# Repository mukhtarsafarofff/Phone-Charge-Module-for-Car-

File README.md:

(ENG)   Actually the MC34063 is the heart of many products that today need a DC-DC converter, that is, a direct voltage converter. The MC34063 is an extremely versatile electronic component that has gained wide acceptance in the electronics world.

The circuit shows the MC34063 configuration as a step-down regulator and in this configuration the output voltage is given by the following formula :
Vout = 1.25 * (1 + R2 / R1)
In our case R2 = 3.6k and R1 = 1.2K so Vout gives us exactly 5 Volts! To transform our circuit into a USB charger, simply connect a USB terminal to the output by soldering the cables with the correct pinout.  Its versatility is accompanied by a very convenient price which is an interesting combination. It is a switching regulator that, unlike linear regulators (such as the LM7805), does not dissipate much heat. In my case, my phone needs a charger at 5VDC, that is, the same voltage that a USB port provides us. Because of this, my faulty charger circuit was designed to provide such a voltage at a current of 500mA. That is, it is an oscillator that chops (or divides into portions) the input voltage, according to the required output voltage value want.

(DEU)  Tatsächlich ist der MC34063 das Herzstück vieler Produkte, die heute einen DC-DC-Wandler benötigen, also einen Gleichspannungswandler. Der MC34063 ist eine äußerst vielseitige elektronische Komponente, die in der Elektronikwelt weit verbreitet und akzeptiert ist. Seine Vielseitigkeit ist mit einem sehr günstigen Preis verbunden, was eine interessante Kombination darstellt.  Es handelt sich um einen Schaltregler, der im Gegensatz zu linearen Reglern (wie dem LM7805) nicht viel Wärme abgibt. In meinem Fall benötigt mein Telefon ein Ladegerät mit 5 VDC, also der gleichen Spannung, die ein USB-Port liefert. Deshalb wurde mein fehlerhafter Ladegerätkreis so entworfen, dass er eine solche Spannung bei einem Strom von 500 mA liefert.  Mit einigen Änderungen können wir den Schaltkreis, den ich später besprechen werde, anpassen, um verschiedene Spannungen zu liefern. With a few changes we can adapt the circuit I will discuss later to provide different voltages.
The chip used is basically the heart of a switched power supply (or switching regulator).

Der verwendete Chip ist im Grunde das Herzstück eines Schaltnetzteils (oder Schaltreglers).Das heißt, er ist ein Oszillator, der die Eingangsspannung entsprechend dem benötigten Ausgangsspannungswert zerkleinert (oder in Portionen teilt).Die Schaltung zeigt die Konfiguration des MC34063 als Abwärtswandler, und in dieser Konfiguration wird die Ausgangsspannung durch die folgende Formel bestimmt:
Vout = 1,25 * (1 + R2 / R1)
In unserem Fall beträgt R2 = 3,6 k und R1 = 1,2 k, sodass Vout uns genau 5 Volt liefert! Um unseren Schaltkreis in ein USB-Ladegerät zu verwandeln,

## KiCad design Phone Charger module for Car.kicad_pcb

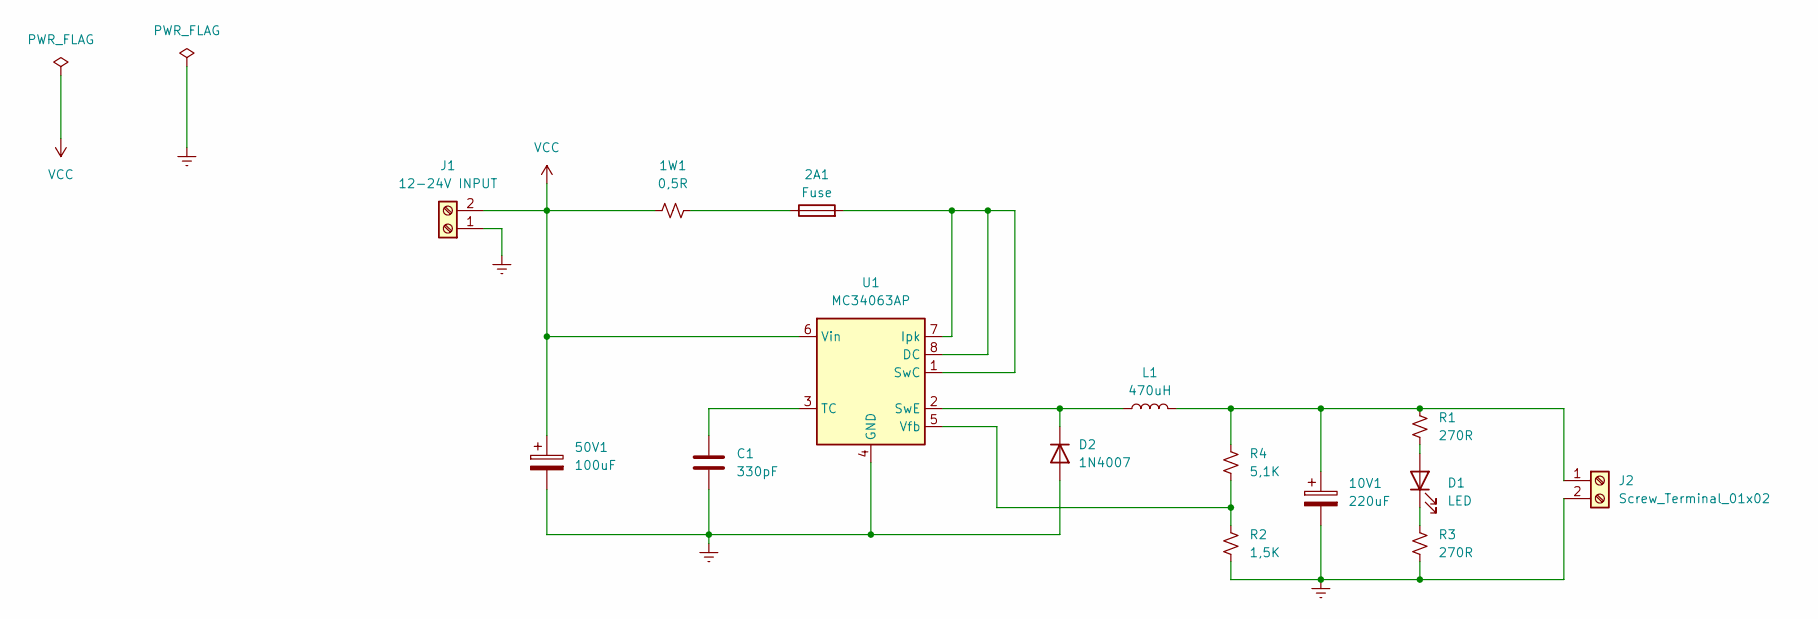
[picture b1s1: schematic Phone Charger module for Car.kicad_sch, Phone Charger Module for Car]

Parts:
1W1: 0,5R; R_Axial_DIN0614_L14.3mm_D5.7mm_P15.24mm_Horizontal
2A1: Fuse; Fuse_Bourns_MF-RG1000
10V1: 220uF; CP_Radial_D13.0mm_P7.50mm
50V1: 100uF; CP_Radial_D13.0mm_P7.50mm
C1: 330pF; C_Disc_D9.0mm_W5.0mm_P7.50mm
D1: LED; LED_D5.0mm
D2: 1N4007; D_DO-41_SOD81_P10.16mm_Horizontal
J1: 12-24V INPUT; TerminalBlock_bornier-2_P5.08mm
J2: Screw_Terminal_01x02; TerminalBlock_bornier-2_P5.08mm
L1: 470uH; L_Toroid_Horizontal_D12.7mm_P20.00mm_Diameter14-5mm_Amidon-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
R1, R3: 270R; R_Axial_DIN0309_L9.0mm_D3.2mm_P15.24mm_Horizontal
R2: 1,5K; R_Axial_DIN0309_L9.0mm_D3.2mm_P15.24mm_Horizontal
R4: 5,1K; R_Axial_DIN0309_L9.0mm_D3.2mm_P15.24mm_Horizontal
U1: MC34063AP; DIP-8_W7.62mm

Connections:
Earth: 10V1.2, 50V1.2, C1.2, D2.2 (A), J1.1, J2.2, R2.2, R3.2, U1.4 (GND)
unnamed: 1W1.2, 2A1.1
unnamed: D1.2 (A), R1.2
unnamed: D1.1 (K), R3.1
unnamed: D2.1 (K), L1.1, U1.2 (SwE)
unnamed: 10V1.1, J2.1, L1.2, R1.1, R4.1
unnamed: 2A1.2, U1.1 (SwC), U1.7 (Ipk), U1.8 (DC)
unnamed: C1.1, U1.3 (TC)
unnamed: R2.1, R4.2, U1.5 (Vfb)
VCC: 1W1.1, 50V1.1, J1.2, U1.6 (Vin)

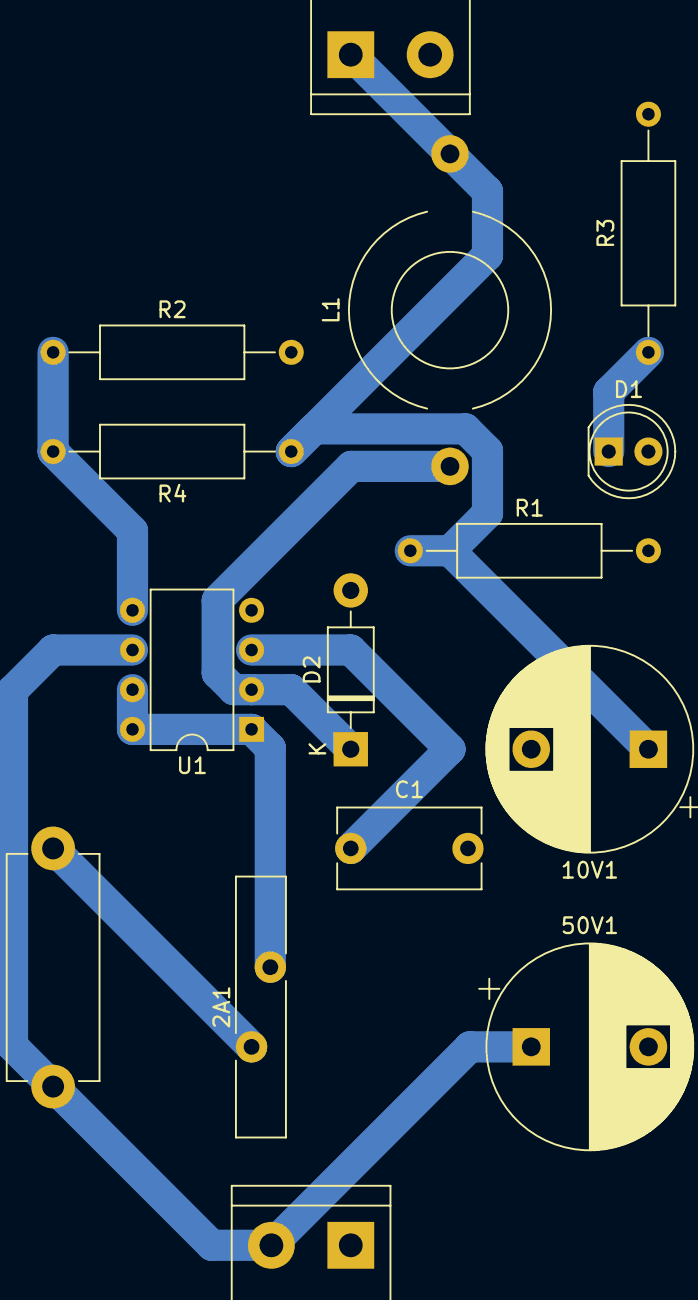
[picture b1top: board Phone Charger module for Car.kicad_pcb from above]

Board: 2 copper layers, 15 parts (0 on the bottom side), 10 nets.

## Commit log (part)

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2024-03-29 Phone Charger Module is accomplished
